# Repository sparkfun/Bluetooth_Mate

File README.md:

Bluetooth Mate
==============

<table class="table table-hover table-striped table-bordered">
  <tr align="center">
   <td></td>
   <td></td>
  </tr>
  <tr align="center">
    <td><a href="https://www.sparkfun.com/products/9358">Bluetooth Mate Gold: RN-41 module (WRL-09358)</a></td>
    <td><a href="https://www.sparkfun.com/products/12576">Bluetooth Mate Silver: RN-42 module (WRL-12576)</a></td>
  </tr>
</table>

These bluetooth wireless modems work as a TTL serial (RX/TX) pipe and are designed to mate directly with [Arduino Pro](https://www.sparkfun.com/products/10915), [Pro Mini](https://www.sparkfun.com/products/11114) and [LilyPad](https://www.sparkfun.com/products/9266) boards. 

Repository Contents
-------------------

* **/Hardware** - All Eagle design files (.brd, .sch)

Documentation
--------------
* **[Hookup Guide](https://learn.sparkfun.com/tutorials/using-the-bluesmirf)** - Basic hookup guide for the BlueSMiRF and Bluetooth Mate.
* **[SparkFun 3D Model repo](https://github.com/sparkfun/3D_Models)** - 3D models of SparkFun products. 

Product Versions
----------------
* [WRL-12576](https://www.sparkfun.com/products/12576)- Bluetooth Mate Silver: RN-42 module
* [WRL-09358](https://www.sparkfun.com/products/9358)- Bluetooth Mate Gold: RN-41 module
* [WRL-10393](https://www.sparkfun.com/products/10393)- Bluetooth Mate Silver: RN-42 module (RETIRED)

License Information
-------------------
The hardware is released under [Creative Commons Share-alike 3.0](http://creativecommons.org/licenses/by-sa/3.0/).

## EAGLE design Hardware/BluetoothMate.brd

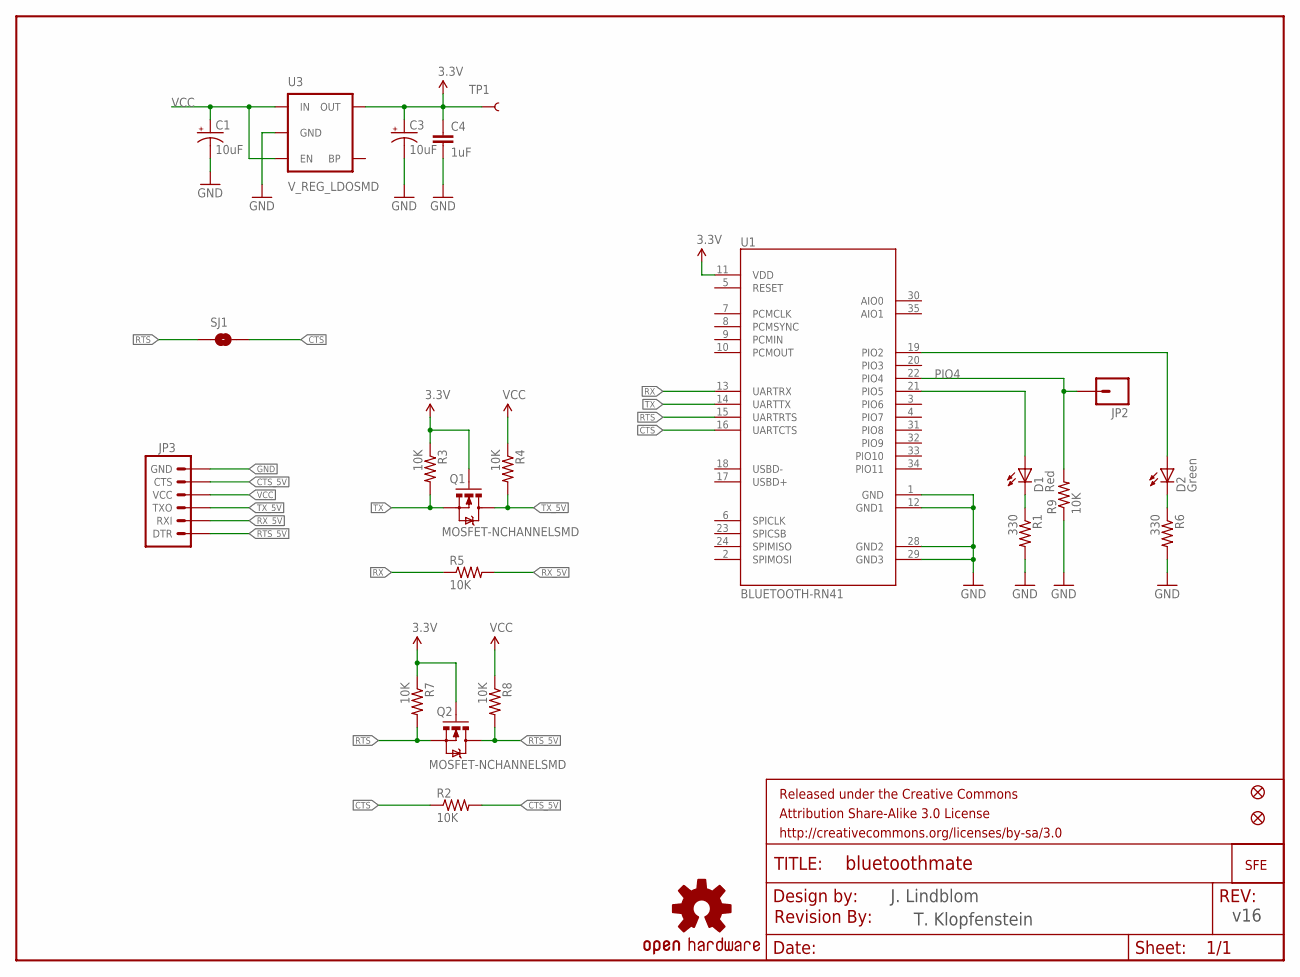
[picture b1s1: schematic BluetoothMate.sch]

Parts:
C1, C3: 10uF; EIA3216
C4: 1uF; 0603-CAP
D1: Red; LED-0603
D2: Green; LED-0603
FRAME1: FRAME-LETTER; CREATIVE_COMMONS
JP1, JP4: FIDUCIAL1X2.5; FIDUCIAL-1X2.5
JP2: M01SMDNS; 1X01NS
JP3: ARDUINO_SERIAL_PROGRAMPTH; 1X06
LOGO1: OSHW-LOGOS; OSHW-LOGO-S
Q1, Q2: MOSFET-NCHANNELSMD; SOT23-3
R1, R6: 330; 0603-RES
R2, R3, R4, R5, R7, R8, R9: 10K; 0603-RES
SJ1: SOLDERJUMPERNO; SJ_2S-NO
TP1: TEST-POINT3X5; PAD.03X.05
U1: BLUETOOTH-RN41; RN41
U3: V_REG_LDOSMD; SOT23-5
U$1: LOGO-SFENEW; SFE-NEW-WEBLOGO
U$2: REVISION

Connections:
3.3V: C3.A (+), C4.1, Q1.1 (G), Q2.1 (G), R3.1, R7.1, TP1.P$1, U1.11 (VDD), U3.5 (OUT)
CTS: R2.1, SJ1.2, U1.16 (UARTCTS)
CTS_5V: JP3.5 (CTS), R2.2
D1: D1.C, R1.1
D2: D2.C, R6.1
GND: C1.C (-), C3.C (-), C4.2, JP3.6 (GND), R1.2, R6.2, R9.1, U1.1 (GND), U1.12 (GND1), U1.28 (GND2), U1.29 (GND3), U3.2 (GND)
unnamed: D1.A, U1.21 (PIO5)
unnamed: D2.A, U1.19 (PIO2)
PIO4: JP2.1, R9.2, U1.22 (PIO4)
RTS: Q2.2 (S), R7.2, SJ1.1, U1.15 (UARTRTS)
RTS_5V: JP3.1 (DTR), Q2.3 (D), R8.2
RX: R5.1, U1.13 (UARTRX)
RX_5V: JP3.2 (RXI), R5.2
TX: Q1.2 (S), R3.2, U1.14 (UARTTX)
TX_5V: JP3.3 (TXO), Q1.3 (D), R4.2
VCC: C1.A (+), JP3.4 (VCC), R4.1, R8.1, U3.1 (IN), U3.3 (EN)

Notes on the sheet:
J. Lindblom
v16
T. Klopfenstein

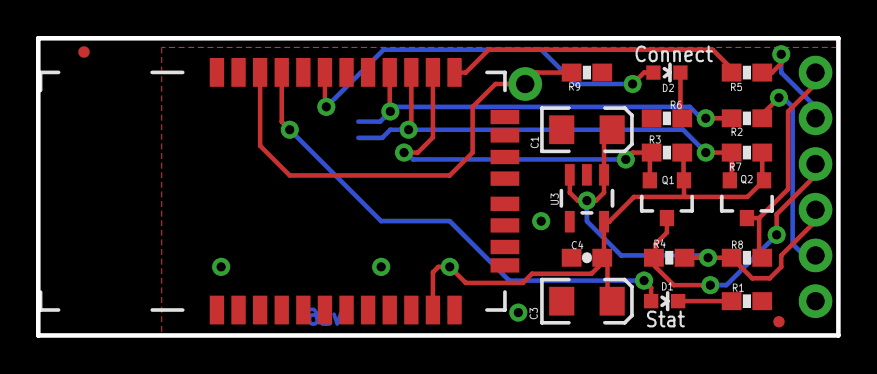
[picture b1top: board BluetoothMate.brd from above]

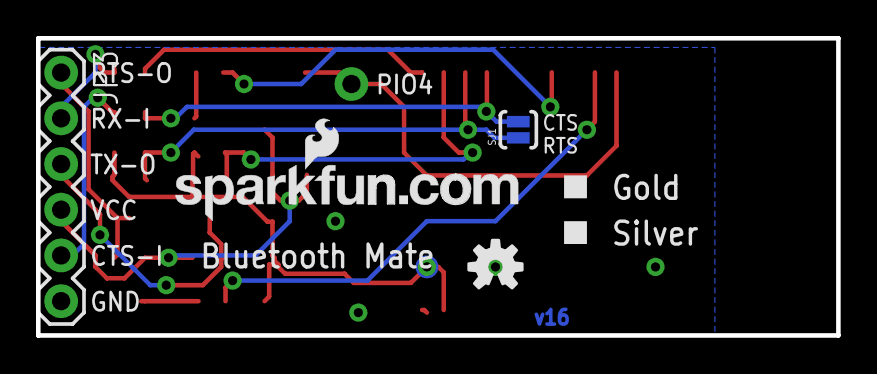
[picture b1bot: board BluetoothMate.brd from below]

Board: 2 copper layers, 44.5 x 16.5 mm, 28 parts (5 on the bottom side), 16 nets.

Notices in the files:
parts and their libraries:
SparkFun-RF: Licensing: CC v3.0 Share-Alike You are welcome to use this library for commercial purposes.
SparkFun-Aesthetics: Released under the Creative Commons Attribution Share-Alike 3.0 License
SparkFun-Aesthetics: Released under the Creative Commons
